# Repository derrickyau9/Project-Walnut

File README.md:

# Project Walnut

**They made the leaf. We cracked the nut.**

**OPEN HARDWARE. · OPEN FIRMWARE. · OPEN PHOTOGRAPHY.**

Project Walnut is an effort to build a professional camera ecosystem that belongs to its users. Photographers and developers should be able to understand, manufacture, repair, modify and extend their equipment, and keep maintaining it after its original maker moves on.

Project Walnut 希望建立真正属于用户、由社区共同发展的专业数码相机生态。摄影师不应只能使用被允许的功能；开发者不应只能面对无法理解的黑箱；设备的寿命也不应完全取决于制造者是否继续支持它。

Walnut，核桃。我们希望打开设备的外壳与黑箱，让硬件、固件和摄影工作流都成为用户可以理解、维修、修改和持续创造的工具。

[镜像下载 / Releases](https://github.com/derrickyau9/Project-Walnut/releases) · [项目命名](docs/product/naming.md) · [产品规划](docs/product/ff1-prd.md) · [相机功能说明](docs/product/camera-apps.md) · [硬件工程](hardware/README.md) · [构建系统](system/bsd-buildroot/README.md)

## 为什么做这件事 / Why it exists

我们希望让功能的边界取决于硬件能力与社区的创造力，让更新、维修、适配和长期维护成为用户可以参与的事情。摄影始终是第一功能；开放接口和可编程工作流服务于拍摄，而不是让相机成为一个通用管理后台。

保有独立研究、修改和发布成果的空间，让设备的控制权与长期维护能力属于用户。

The goal is an open platform whose limits are determined by hardware and engineering, with documented interfaces and a community that can sustain it. Photography comes first. Programmability should make the camera more useful to its owner.

成功不只是造出一台相机。更重要的标准是：其他开发者能够依据公开的设计和明确的开放许可，制造自己的相机、修改系统、扩展功能并继续维护，无须逐次向原作者请求授权。

## 一个计划，三个层次 / Three connected layers

| 层次 / Layer | 定位 / Purpose |
| --- | --- |
| **Project Walnut** | 开放摄影生态、工程资料与社区协作的整体计划。The wider ecosystem and engineering effort. |
| **DaOS Camera** | 面向摄影的操作系统集成、硬件抽象、原生相机服务、界面与工作流。The camera software platform. |
| **Walnut FF-1** | 计划中的第一款整机，以可用的专业全画幅无反相机为目标。The first planned camera body and architecture proving ground. |

### 开放的方向 / What we are building toward

- **Open Hardware**：可编辑的机身、电路板、传感器接口、模块化结构与制造资料。
- **Open Firmware**：可研究、编译、修改和维护的 ARM64 相机软件，包含 BSD/Unix 系统集成。
- **Open Photography**：公开采集、RAW、图像处理、校准绑定和相关开发接口。
- **Modular Lens Mount**：可更换卡口模组、清楚的接口边界与适配机制。
- **Community Development**：让制造、维修、移植、功能扩展和长期维护能够由社区接续。

## 当前进度 / Current status

**这是研发中的原型项目，尚不是完成的全画幅相机产品。** FF-1 的真实传感器、FPGA 高速采集、实测色彩校准、镜头电子控制、自动对焦和其他机身硬件能力仍有独立的工程验证工作。

当前可运行的软件原型包含 C++17 相机服务、SQLite 日志、Bayer/DNG 合成采集、Qt Quick 界面、保留媒体工作流和 USB 开发工具。树莓派研发设备已运行 FreeBSD ARM64 相机界面，并验证过 DSI 显示、触摸和 USB ADB；图像源仍为 **HF-Sim 合成场景**。

The running prototype uses **HF-Sim**, a synthetic image source. Screenshots and simulator captures demonstrate software behavior; they do not establish physical sensor acquisition, calibrated color, recording performance or production hardware readiness.

| 工程范围 / Area | 当前边界 / Present boundary |
| --- | --- |
| 相机服务、合成 RAW 与日志 | 已有原生实现和自动测试。Native implementation and tests exist. |
| Qt 相机界面 | 摄影、回放、工作区、工作流及系统页面持续迭代。Camera-first interface under active development. |
| 树莓派显示、触摸、USB | 研发设备有实机记录；每份 Release 镜像仍以自己的验证说明为准。Development-board evidence is separate from image acceptance. |
| USB 急救与异常回退 | 已在固定研发设备验证独立 RAM 急救、USB 回连和正常系统恢复；绑定设备的恢复镜像不能当作通用整卡镜像。 |
| 板载 Wi-Fi | 实机连接尚未验证成功。Physical connectivity remains unfinished. |
| 双轴水平仪 | 提供姿态显示与数据输入接口；当前没有已验证的实机 IMU 数据或校准，演示数据独立标示。 |
| OpenBSD 迁移 | 候选完成 ARM 虚拟机启动、认证 SSH 和传输测试；尚未替换实机主系统。Experimental migration, not the released main OS. |
| FF-1 整机与真实图像链 | 硬件设计、接口和验证工作仍在推进。Hardware and acquisition work remains in progress. |

## 当前软件功能 / Software features

### 拍摄与工作区 / Capture and workspaces

- 首屏优先启动取景；菜单、回放、工具、工作台和键盘首次使用时加载并保留。离线启动对比和实机验证边界见[启动性能记录](docs/performance/startup.md)。
- 摄影优先的取景界面、曝光与增益设置、网格、明暗主题和可隐藏任务栏。
- 可开关的双轴电子水平仪，显示横滚、俯仰及调平状态；缺失或过期的姿态数据会失效，演示角度明确标记 DEMO。真实 IMU 接入与校准仍需实机验证。
- 十二格 Q 菜单、My Menu、C1–C3 工作区、六种布局、工作区导入导出及 Fn 输入边界。
- 原生相机控制、独占控制租约、参数确认和原请求 ID 恢复；未知结果不会自动重拍。
- 独立的合成实时预览及 Bayer/DNG 保存。预览配置不等于实测帧率或真实传感器能力。

### 回放与图像工作流 / Playback and image workflow

- 保留照片浏览、原像素分块查看、元数据、评分、保护和可恢复移除。
- 调整参数以旁车文件保存；曝光、对比度、饱和度、旋转和居中裁切保留原始 RAW。
- DNG 导出，以及有尺寸上限、未校准的 SDR JPEG 校样导出。
- 图像风格、配方编辑、包围拍摄计划、执行进度、暂停、继续、取消和任务汇总。

### 联机与设备工具 / Connectivity and device tools

- USB 开发入口、相机联机协议、预览和媒体传输接口，以及配对式网络联机的软件实现。
- 系统偏好、配置备份恢复、更新包检查、诊断和能力边界展示。
- 触摸键盘、离线拼音输入和终端界面。需要目标系统服务或硬件的功能会显示其可用状态。

界面中存在的视频参数工作区不表示视频采集和编码已经完成；网络页面也不表示板载无线已通过实机验收。

## 界面截图 / UI screenshots

中英文截图按相同功能对应展示。取景示例与回放、比较、评分和编辑演示使用项目对话提供的三张 JPEG 照片，通过实际 Qt 界面渲染。底层拍摄控制与合成 RAW 仍由 HF-Sim 提供；样片不作为传感器或硬件性能证明。

The English and Simplified Chinese galleries cover the same interface states. User-provided JPEG samples demonstrate the viewfinder, playback and editing through the actual Qt UI. Capture control and synthetic RAW remain HF-Sim; the sample photographs are not sensor or hardware validation.

<!-- UI_GALLERY_START -->
**50 个对应功能界面 × 2 种语言，共 100 张截图。** [完整图库和源码对应清单 / Gallery and source manifest](docs/screenshots/README.md)

| English | 简体中文 |
| --- | --- |
| **Capture and sample preview** | **拍摄与示例预览** |
|  |  |
| **Level unavailable** | **水平仪未连接** |
|  |  |
| **Level aligned demo** | **水平仪水平示例** |
|  |  |
| **Level tilted demo** | **水平仪倾斜示例** |
|  |  |
| **Application taskbar** | **应用任务栏** |
|  |  |
| **Exposure and analogue gain** | **曝光与增益** |
|  |  |
| **Photo quick controls** | **照片十二格快捷面板** |
|  |  |
| **Video layout and capability limits** | **视频布局与能力边界** |
|  |  |
| **Quick-control assignment** | **快捷功能分配** |
|  |  |
| **My Menu** | **我的菜单** |
|  |  |
| **C1–C3 custom profiles** | **C1–C3 记忆** |
|  |  |
| **Fn and dial mappings** | **Fn 与拨轮映射** |
|  |  |
| **Workspace configuration sharing** | **工作台配置分享** |
|  |  |
| **Exposure settings** | **曝光菜单** |
|  |  |
| **Image and RAW** | **图像与 RAW** |
|  |  |
| **Display and framing** | **显示与构图** |
|  |  |
| **Storage information** | **存储信息** |
|  |  |
| **Wireless network** | **无线网络** |
|  |  |
| **System preferences** | **系统偏好** |
|  |  |
| **Configuration backup and restore** | **配置备份与恢复** |
|  |  |
| **Application update and rollback** | **应用更新与回退** |
|  |  |
| **Developer and diagnostics** | **开发与诊断** |
|  |  |
| **Controlled tethering** | **受控联机** |
|  |  |
| **Terminal entry** | **终端入口** |
|  |  |
| **Touch keyboard** | **触摸键盘** |
|  |  |
| **Capabilities and performance** | **能力与性能** |
|  |  |
| **Runtime diagnostics** | **运行诊断** |
|  |  |
| **Capture plans** | **拍摄计划** |
|  |  |
| **Exposure-bracket plan** | **曝光包围计划** |
|  |  |
| **Interval and calibration sequences** | **间隔与校准序列** |
|  |  |
| **Photo rendering looks** | **照片显示风格** |
|  |  |
| **Background task center** | **后台任务中心** |
|  |  |
| **Image processing workspace** | **图像计算工作台** |
|  |  |
| **Image processing operations** | **图像处理功能** |
|  |  |
| **Photo library** | **照片库** |
|  |  |
| **Multi-selection and batch management** | **多选与批量管理** |
|  |  |
| **Photo playback** | **照片回放** |
|  |  |
| **Side-by-side and pixel inspection** | **并排与像素查看** |
|  |  |
| **Non-destructive tone editing** | **非破坏明暗编辑** |
|  |  |
| **Rotation and crop** | **旋转与裁切** |
|  |  |
| **White balance and RGB** | **白平衡与 RGB** |
|  |  |
| **Tone curve** | **色调曲线** |
|  |  |
| **Custom styles** | **自定义风格** |
|  |  |
| **Edit history** | **编辑历史** |
|  |  |
| **Batch export** | **批量导出** |
|  |  |
| **File browser and copy import** | **文件浏览与复制导入** |
|  |  |
| **Photo library actions** | **照片库工具** |
|  |  |
| **Photo ratings** | **照片评分** |
|  |  |
| **Photo metadata** | **照片元数据** |
|  |  |
| **Permanent-delete confirmation** | **永久清空确认** |
|  |  |
<!-- UI_GALLERY_END -->

## 运行源码 / Run from source

需要 Python 3.12、CMake、C++17 编译器，以及 Qt/PyQt 运行时。原生服务和界面各自有明确的构建入口：

```sh
python -m pip install -r requirements-ui.txt
python tools/build_native.py --build-dir build/native
```

Windows 默认 CMake Release 输出的启动示例：

```powershell
python ui/on-device/main.py --native-command build/native/Release/hf-camerad.exe --data-dir var/hf-device
```

可使用 `--language en_US` 或 `--language zh_CN` 选择界面语言，也可在系统偏好中切换。语言设置不会改写文件名、命令、路由或用户输入。

样片取景演示可加 `--demo-image ui/on-device/demo-images/coast.jpg`。水平仪演示可加 `--demo-attitude 0 0`，会明确标记 DEMO；实际姿态输入使用 `--attitude-file PATH`，两种姿态输入方式互斥。照片库可复制导入 [三张示例照片](ui/on-device/demo-images/README.md)，用于回放、比较、评分和非破坏编辑；示例预览会明确标示其来源。

Unix 构建通常输出 `build/native/hf-camerad`；将 `--native-command` 指向该文件。每个并行实例使用独立数据目录。详见 [界面说明](ui/on-device/README.md) 与 [原生相机说明](camera/native/README.md)。

## 固件镜像 / Firmware images

**镜像放在 [GitHub Releases](https://github.com/derrickyau9/Project-Walnut/releases)，不进入 Git 源码历史。** 每个镜像附带 SHA-256、适用硬件、构建来源、包含功能及验证限制。

Full-card images and partition-repair images are different artifacts. Follow the individual release instructions and checksums. Experimental OpenBSD payloads and device-bound recovery backups are not general-purpose firmware releases.

当前整卡镜像面向树莓派 4 ARM64 开发平台及其指定显示配置。FF-1 整机固件、板载 Wi-Fi 和真实传感器能力不因发布镜像而自动成为已完成项目。

Project Walnut 新预览的样片演示、水平仪接口、固定构建输入、授权公钥和实机验证边界见 [镜像构建与使用说明 / Preview guide](docs/releases/walnut-preview-002.md)。

## 目录 / Repository map

| 目录 | 内容 |
| --- | --- |
| `hardware/` | 机身、板卡、传感器接口及导入设计的来源记录 |
| `fpga/` | 采集数据链 RTL、测试台和接口工程 |
| `firmware/` | 辅助控制器固件与边界定义 |
| `camera/` | 原生相机服务、RAW/DNG、校准、媒体与图像处理 |
| `ui/on-device/` | 摄影界面、工作区、工作流与设备工具 |
| `daos/` | 相机协议、能力接口与扩展基础 |
| `system/` | BSD/ARM64、镜像构建、USB 和恢复集成 |
| `tests/`、`tools/` | 自动测试、构建与验证工具 |
| `docs/` | 产品、架构、验证说明与完整截图 |
| `licenses/` | 来源、第三方条款与项目授权状态 |

`build/`、`var/`、虚拟机、凭据、私人备份和用户照片均不属于 Git 源码内容。

## 参与和授权 / Contributing and licensing

欢迎围绕摄影体验、可维修硬件、采集接口、图像管线、系统移植、测试和文档开展协作。请区分提案、模拟器结果、虚拟机结果和实机结果，并保留第三方来源与许可声明。

当前仓库为私有研发仓库。开放硬件、软件、SDK 和文档的授权方案记录在 [许可清单](licenses/README.md)；其中待确认的项目不能当作已经生效的统一授权。第三方组件继续遵循各自条款。项目的开放目标包括明确的制造、修改和再分发权利。

**让相机成为用户可以理解、控制、修改和创造的工具。**

**They made the leaf. We cracked the nut.**

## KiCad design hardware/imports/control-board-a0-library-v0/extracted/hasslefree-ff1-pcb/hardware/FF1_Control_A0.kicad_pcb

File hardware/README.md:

# Walnut FF-1 hardware

These materials belong to Project Walnut's planned first camera body,
[Walnut FF-1](../docs/product/ff1-prd.md).

This directory now includes preserved, editable mechanical and control-board prototype sources, plus a sensor-interface study. Read the [integration review](interface-review.md) and [provenance manifest](imports/provenance.json). These sources have not established a manufacturable or electrically/optically validated camera. Do not manufacture from the imported concepts as a released system.

## Gate to a first board

Before schematic freeze, obtain and record a supplier's written answers for
sample availability and ongoing supply; schematic/pinout and supply sequencing;
reference clocks; control registers and effective-setting timing; receiver
protocol and lane rate; pixel packing, active area and optical black; sensor
package and optical stack; evaluation hardware; and permission to publish the
driver, initialization, FPGA receiver and necessary board files. Record any NDA
constraints separately. No quotation or permission is represented as obtained.

The first sensor module must have a separately supported mechanical reference,
safe access to power/clock/reset/control test points, and an identified thermal
path. Specify voltages, tolerances, current limits, PCB stackup, connector and
signal integrity only after acquiring the device data and selecting parts.
Sensor removal requires power-down and subsequent optical recalibration.

## First light protocol

Keep the sensor protected and use current-limited supplies. Record equipment,
board revision, firmware hash and environmental conditions for each attempt.
Check rails and sequence against the actual device data, then clock, reset and
control communication; establish receiver lock; validate frames and counters;
inspect Bayer and controlled exposure response; validate DNG pixels; only then
evaluate preview. Escalate discrepancies instead of masking damaged frames.

Before fabrication, independent schematic and layout reviews must cover power,
clocking, return paths, isolation, thermal effects, connectors and mechanical
clearance. Obtain the electrical and manufacturing specifications first.

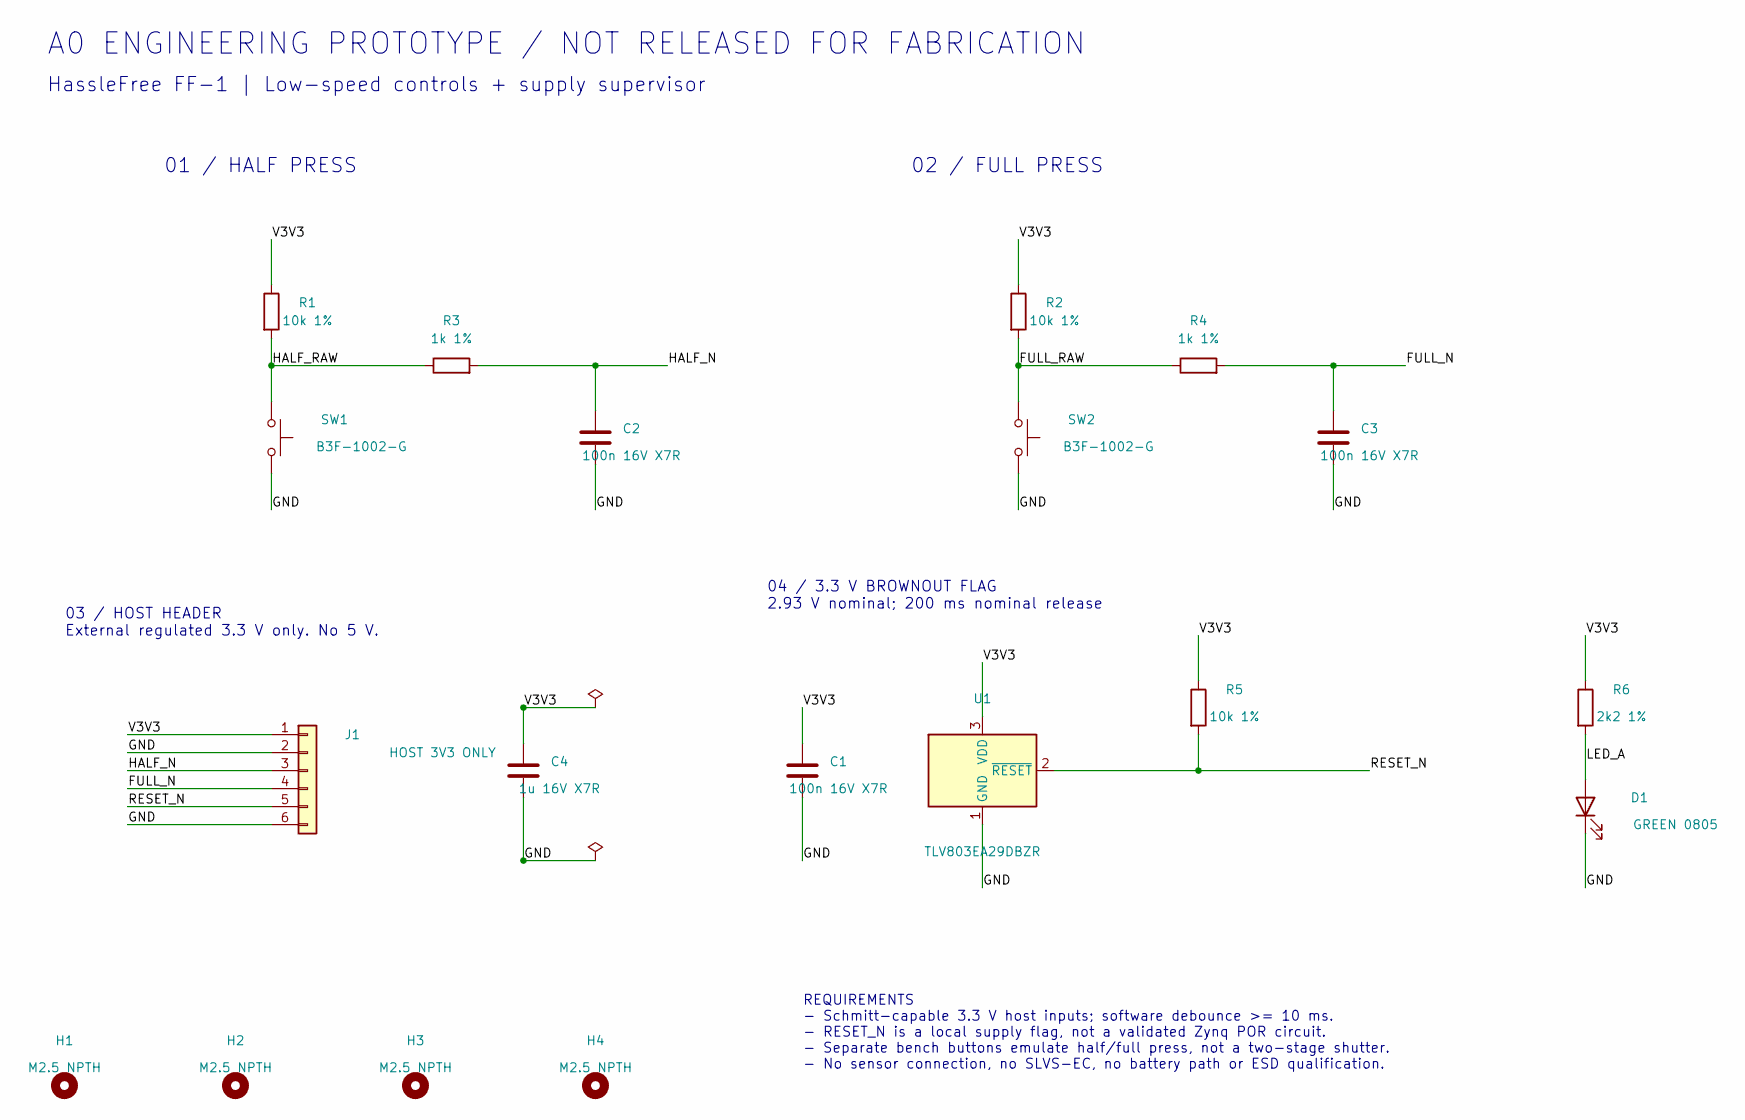
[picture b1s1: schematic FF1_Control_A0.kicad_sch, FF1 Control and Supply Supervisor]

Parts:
C1, C2, C3: 100n 16V X7R; C_0603_1608Metric
C4: 1u 16V X7R; C_0603_1608Metric
D1: GREEN 0805; LED_0805_2012Metric
H1, H2, H3, H4: M2.5 NPTH; MountingHole_2.7mm_M2.5
J1: HOST 3V3 ONLY; PinHeader_1x06_P2.54mm_Vertical
R1, R2, R5: 10k 1%; R_0603_1608Metric
R3, R4: 1k 1%; R_0603_1608Metric
R6: 2k2 1%; R_0603_1608Metric
SW1, SW2: B3F-1002-G; SW_TH_Tactile_Omron_B3F-10xx
U1: TLV803EA29DBZR; SOT-23

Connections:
/FULL_N: C3.1, J1.4, R4.2
/FULL_RAW: R2.2, R4.1, SW2.1
/GND: C1.2, C2.2, C3.2, C4.2, D1.1 (K), J1.2, J1.6, SW1.2, SW2.2, U1.1 (GND)
/HALF_N: C2.1, J1.3, R3.2
/HALF_RAW: R1.2, R3.1, SW1.1
/LED_A: D1.2 (A), R6.2
/RESET_N: J1.5, R5.2, U1.2 (~RESET)
/V3V3: C1.1, C4.1, J1.1, R1.1, R2.1, R5.1, R6.1, U1.3 (VDD)

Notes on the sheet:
01 / HALF PRESS
02 / FULL PRESS
03 / HOST HEADER External regulated 3.3 V only. No 5 V.
04 / 3.3 V BROWNOUT FLAG 2.93 V nominal; 200 ms nominal release
A0 ENGINEERING PROTOTYPE / NOT RELEASED FOR FABRICATION
HassleFree FF-1 | Low-speed controls + supply supervisor
REQUIREMENTS - Schmitt-capable 3.3 V host inputs; software debounce >= 10 ms. - RESET_N is a local supply flag, not a validated Zynq POR circuit. - Separate bench buttons emulate half/full press, not a two-stage shutter. - No sensor connection, no SLVS-EC, no battery path or ESD qualification.

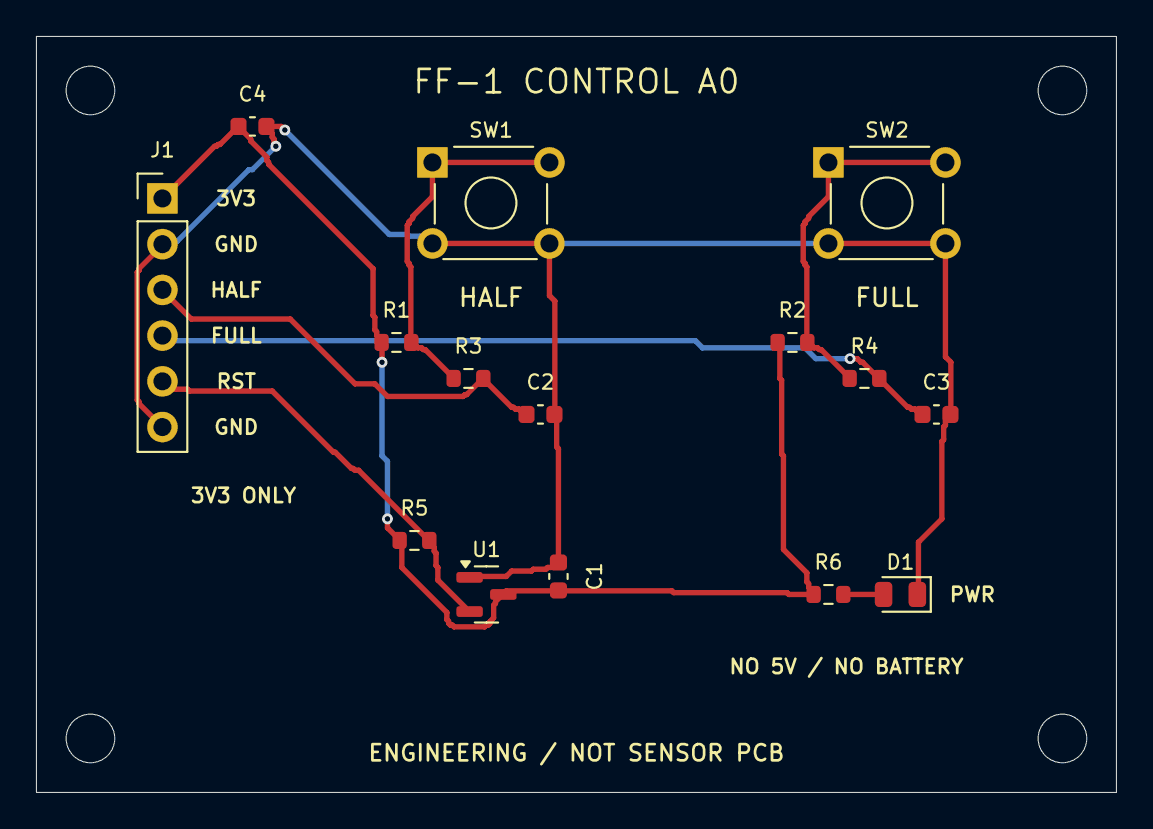
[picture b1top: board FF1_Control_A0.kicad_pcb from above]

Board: 2 copper layers, 60.0 x 42.0 mm, 19 parts (0 on the bottom side), 8 nets.

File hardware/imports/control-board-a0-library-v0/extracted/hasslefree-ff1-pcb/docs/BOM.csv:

References,Quantity,Value,Package,Manufacturer_or_candidate,MPN_or_selection,status,notes
U1,1,2.93V active-low open-drain 200ms,SOT-23,Texas Instruments,TLV803EA29DBZR,Exact electrical part checked,Pin1 GND; pin2 RESET; pin3 VDD. Generic KiCad SOT-23 land pattern requires final assembly review. Do not substitute R/V pinout variants.
SW1 SW2,2,SPST-NO gold contacts,THT 6x6mm,Omron / Aratas,B3F-1002-G,Exact part and hole pattern checked,4.3mm plunger height; 6.5x4.5mm holes; independent buttons; not dual-stage shutter.
R1 R2 R5,3,10k 1% >=0.1W,0603 1608 metric,To select,Parametric component,MPN not finalized,Choose qualified thick-film resistor; no purchasing approval implied.
R3 R4,2,1k 1% >=0.1W,0603 1608 metric,To select,Parametric component,MPN not finalized,Series input filter resistors; not a level shifter or ESD solution.
R6,1,2.2k 1% >=0.1W,0603 1608 metric,To select,Parametric component,MPN not finalized,LED current limiting; actual brightness must be tested.
C1 C2 C3,3,100nF 16V X7R +/-10%,0603 1608 metric,To select,Parametric component,MPN not finalized,C1 local bypass; C2/C3 filter. Confirm effective capacitance at 3.3V bias.
C4,1,1uF 16V X7R +/-10%,0603 1608 metric,To select,Parametric component,MPN not finalized,Local bulk; confirm effective capacitance at 3.3V bias.
D1,1,Green LED,0805 2012 metric,Kingbright,APT2012SGC candidate,Candidate datasheet checked; footprint pending final review,Generic KiCad 0805 footprint; electrical current is conservative; low-current visibility untested.
J1,1,1x6 straight male header 2.54mm,THT pin header,To select,Parametric connector,MPN and mating harness not finalized,Unkeyed bench connector; 1mm holes; verify pin section and assembly height before procurement.
H1 H2 H3 H4,4,2.7mm NPTH mounting holes,M2.5 clearance,PCB fabrication,None,Mechanical feature not component,Prefer insulating fixings; fasteners and host enclosure not supplied.
